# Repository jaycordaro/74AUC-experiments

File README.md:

# 74AUC-experiments
just KiCAD files for a simple test board to test out JLC PCB's 4 layer boards and evaluate 74AUC logic

see https://www.jaycordaro.com/electronics/74auc_ring_osc.html

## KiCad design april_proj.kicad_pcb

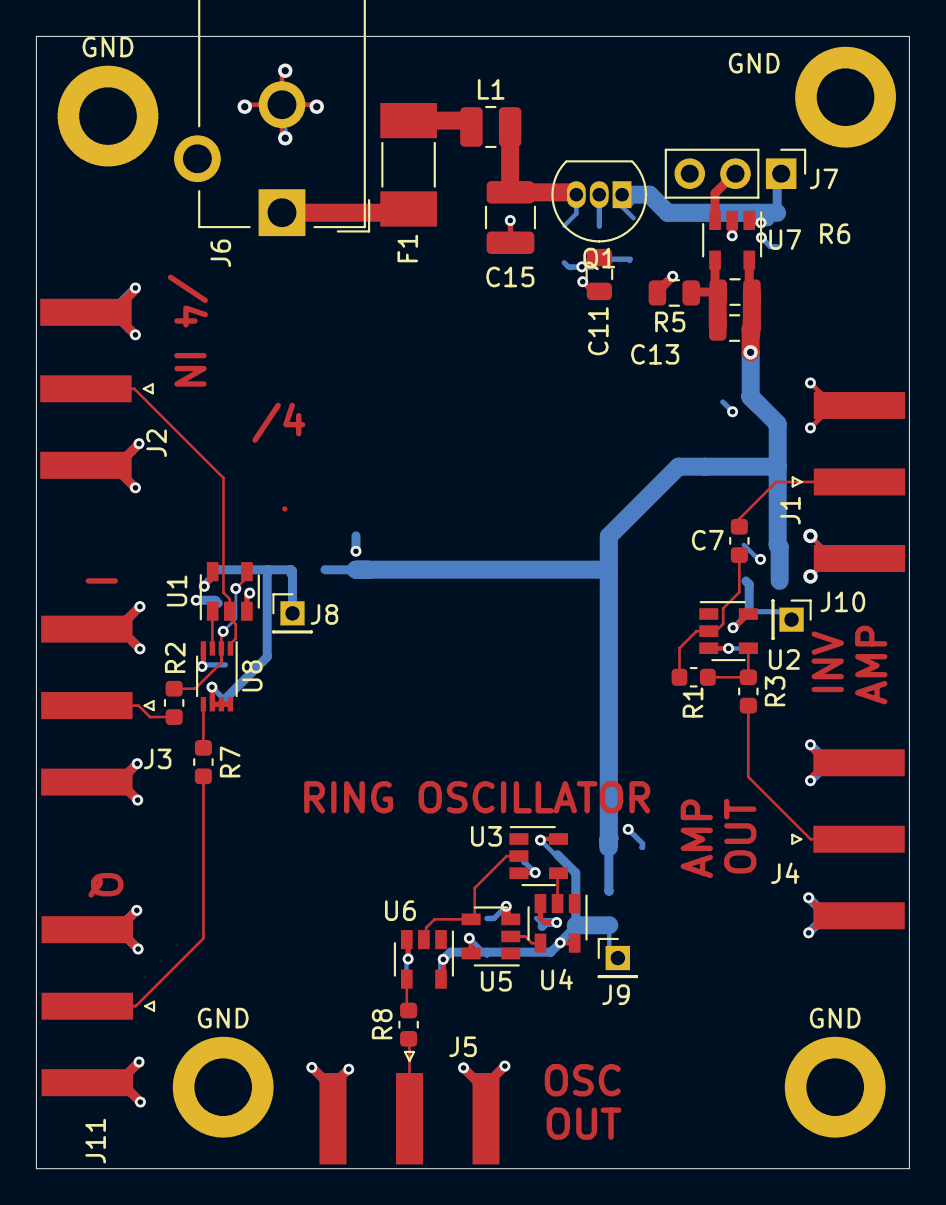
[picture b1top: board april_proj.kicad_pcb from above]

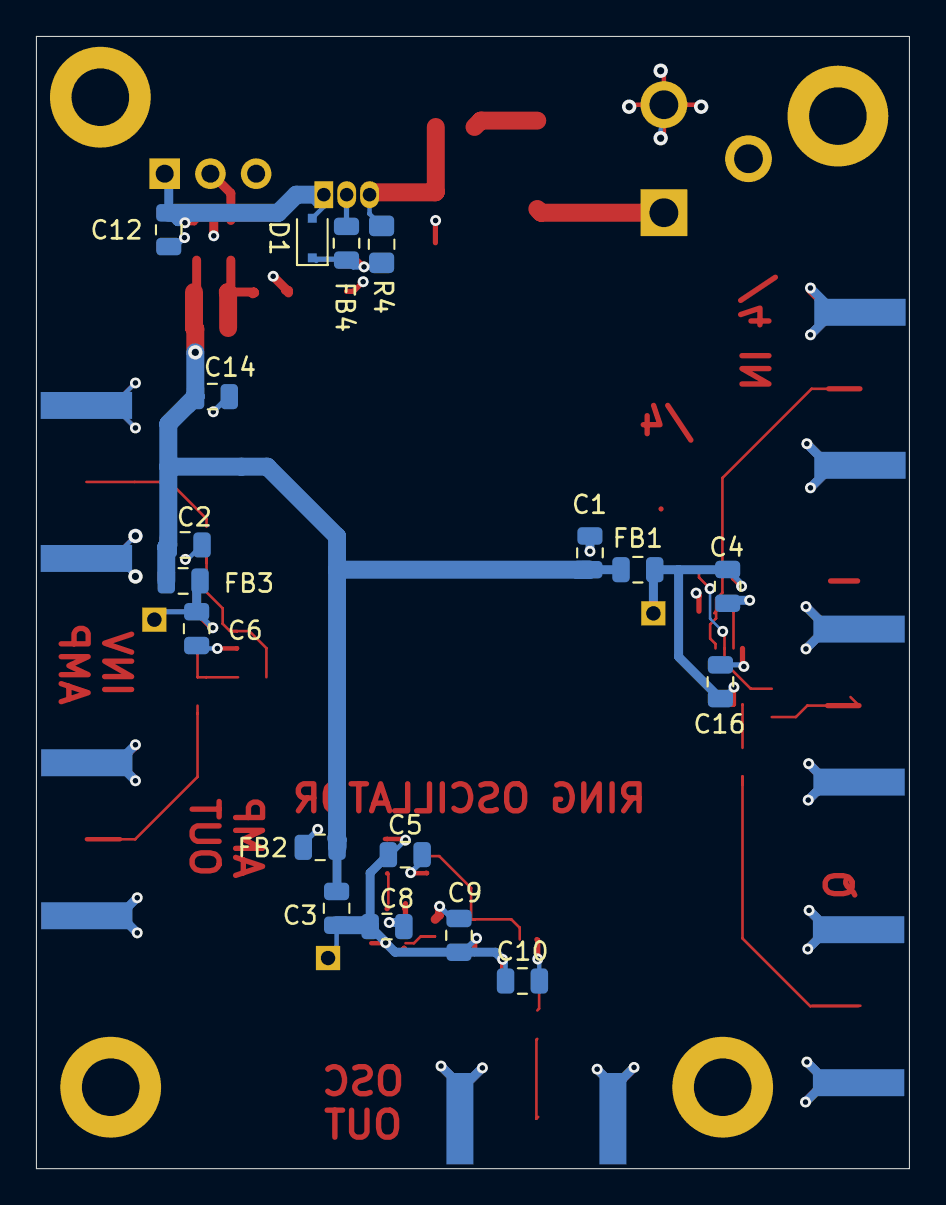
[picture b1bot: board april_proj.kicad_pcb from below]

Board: 4 copper layers, 48.5 x 62.9 mm, 55 parts (18 on the bottom side), 25 nets.

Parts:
C1, C2, C4, C6, C16: .1u; C_0805_2012Metric
C3, C5, C8, C9, C10: .1uF; C_0805_2012Metric
C7: .1u; C_0603_1608Metric
C11: 1.5uF; C_0805_2012Metric
C12: 1uF; R_0805_2012Metric
C13: 1nF; R_0805_2012Metric
C14: 4.7uF; C_0805_2012Metric
C15: 22uF; C_1210_3225Metric
D1: 1N4148; D_SOD-323F
F1: Fuse; Fuse_Littelfuse-NANO2-451_453
FB1, FB2, FB3: Ferrite_Bead; L_0805_2012Metric
FB4: Ferrite_Bead; C_0805_2012Metric
GND: MountingHole_3.2mm_M3_DIN965_Pad
GND#2, GND#3, GND#4: MountingHole_3.2mm_M3_DIN965_Pad
J1, J2, J3, J4, J5, J11: Conn_Coaxial; SMA_Amphenol_132289_EdgeMount
J6: Barrel_Jack; BarrelJack_CUI_PJ-102AH_Horizontal
J7: Conn_01x03_Male; PinHeader_1x03_P2.54mm_Vertical
J8, J9, J10: Conn_01x01_Male; PinHeader_1x01_P2.00mm_Vertical
L1: L; L_1008_2520Metric
Q1: 2N3904; TO-92_Inline
R1: 10M; C_0603_1608Metric
R2, R3, R7, R8: 33; C_0603_1608Metric
R4: 1k; R_0805_2012Metric_Pad1.15x1.40mm_HandSolder
R5: 18k; R_0805_2012Metric
R6: 22.5k; R_0805_2012Metric
U1: 74AUC1G79; SOT-23-5
U2, U3, U4, U5, U6: 74AUC1GU04; SOT-23-5
U7: AP2127K-ADJ; SOT-23-5
U8: 74AUC1G74; VSSOP-8_2.3x2mm_P0.5mm

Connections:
GND: C1.2, C2.2, C3.2, C4.2, C5.2, C6.2, C8.2, C9.2, C10.2, C11.2, C12.2, C14.2, C15.2, C16.2, GND#2.1, GND#3.1, GND#4.1, J1.2, J2.2, J3.2, J4.2, J5.2, J6.2, J7.3, J11.2, R5.1, U1.3, U2.3, U3.3, U4.3, U5.3, U6.3, U7.2, U8.4
unnamed: C7.1, J1.1
unnamed: C7.2, R1.2, U2.2
unnamed: C11.1, D1.1, FB4.2, R4.1
unnamed: C12.1, D1.2, J7.1, Q1.1, U7.1
unnamed: C13.2, R5.2, R6.1, U7.4
unnamed: C15.1, L1.2, Q1.3, R4.2
unnamed: F1.1, L1.1
unnamed: F1.2, J6.1
unnamed: FB4.1, Q1.2
unnamed: J2.1, U1.2, U8.1
unnamed: J3.1, R2.1
unnamed: J4.1, R3.1
unnamed: J5.1, R8.1
unnamed: J7.2, U7.3
unnamed: J11.1, R7.1
unnamed: R1.1, R3.2, U2.4
unnamed: R2.2, U1.4, U8.2
unnamed: R7.2, U8.5
unnamed: R8.2, U6.4
unnamed: U1.1, U8.3
unnamed: U3.2, U5.4, U6.2
unnamed: U3.4, U4.2
unnamed: U4.4, U5.2
VCC: C1.1, C2.1, C3.1, C4.1, C5.1, C6.1, C8.1, C9.1, C10.1, C13.1, C14.1, C16.1, FB1.1, FB1.2, FB2.1, FB2.2, FB3.1, FB3.2, J8.1, J9.1, J10.1, R6.2, U1.5, U2.5, U3.5, U4.5, U5.5, U6.5, U7.5, U8.6, U8.7, U8.8
